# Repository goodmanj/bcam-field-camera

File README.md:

# BCam - Magnetic Field Camera

## About
BCam lets you see see invisible magnetic fields!  It uses an array of magnetic field sensors to map out the strength and direction of magnetic fields passing through it, displaying the fields on an LCD screen in realtime.  It can sense strong permanent magnets and electromagnets, as well as the weak fields from single current-carrying wires, and the Earth's magnetic field.

BCam is based on the [RP2040 Raspberry Pi Pico](https://www.raspberrypi.com/documentation/microcontrollers/pico-series.html) microcontroller, the [TMAG5273](https://www.ti.com/product/TMAG5273) Hall-effect magnetic field sensor, and the [ILI9488](http://www.lcdwiki.com/3.5inch_SPI_Module_ILI9488_SKU:MSP3520) touch LCD screen.  

BCam was originally designed as a teaching tool for physics classrooms.  The [documentation](doc/) includes demos, lab handouts, and other teaching material.

## Build your own!

This repo contains everything you need to build a BCam:
* [2d/](2d/): 2-d design files (label graphics)
* [pcb/](pcb/): Printed circuit board files
* [src/](src/): Arduino source code
* [cad/](cad/): 3-d design files
* [doc/](doc/): Documentation
* [bom.md](bom.md): Bill of materials

BCam is designed to be built by hand.  All surface-mount parts are hand-solderable (some skill required).  The case is 3-d printed.  You can use a desktop CNC machine to mill your own printed circuit board, or have it made by an online board manufacturer such as [JLCPCB](https://jlcpcb.com/), [PCBWay](https://www.pcbway.com/), or [OSHPark](https://oshpark.com/).

BCam was originally developed as a project for [Fab Academy](https://fabacademy.org/), a hands-on global class in rapid prototyping and digital fabrication.  The original project documentation is [archived at Fab Academy's site](https://fabacademy.org/2023/labs/wheaton/students/jason-goodman/final-project/index.html), but is superseded by this repo.

## Copyright and License

Copyright (c) 2023-2025 Jason Goodman <jcgoodman@gmail.com>

This work is licensed under a
[Creative Commons Attribution-NonCommercial-ShareAlike 4.0 International License][cc-by-nc-sa].

[![CC BY-NC-SA 4.0][cc-by-nc-sa-image]][cc-by-nc-sa]

[cc-by-nc-sa]: http://creativecommons.org/licenses/by-nc-sa/4.0/
[cc-by-nc-sa-image]: https://licensebuttons.net/l/by-nc-sa/4.0/88x31.png

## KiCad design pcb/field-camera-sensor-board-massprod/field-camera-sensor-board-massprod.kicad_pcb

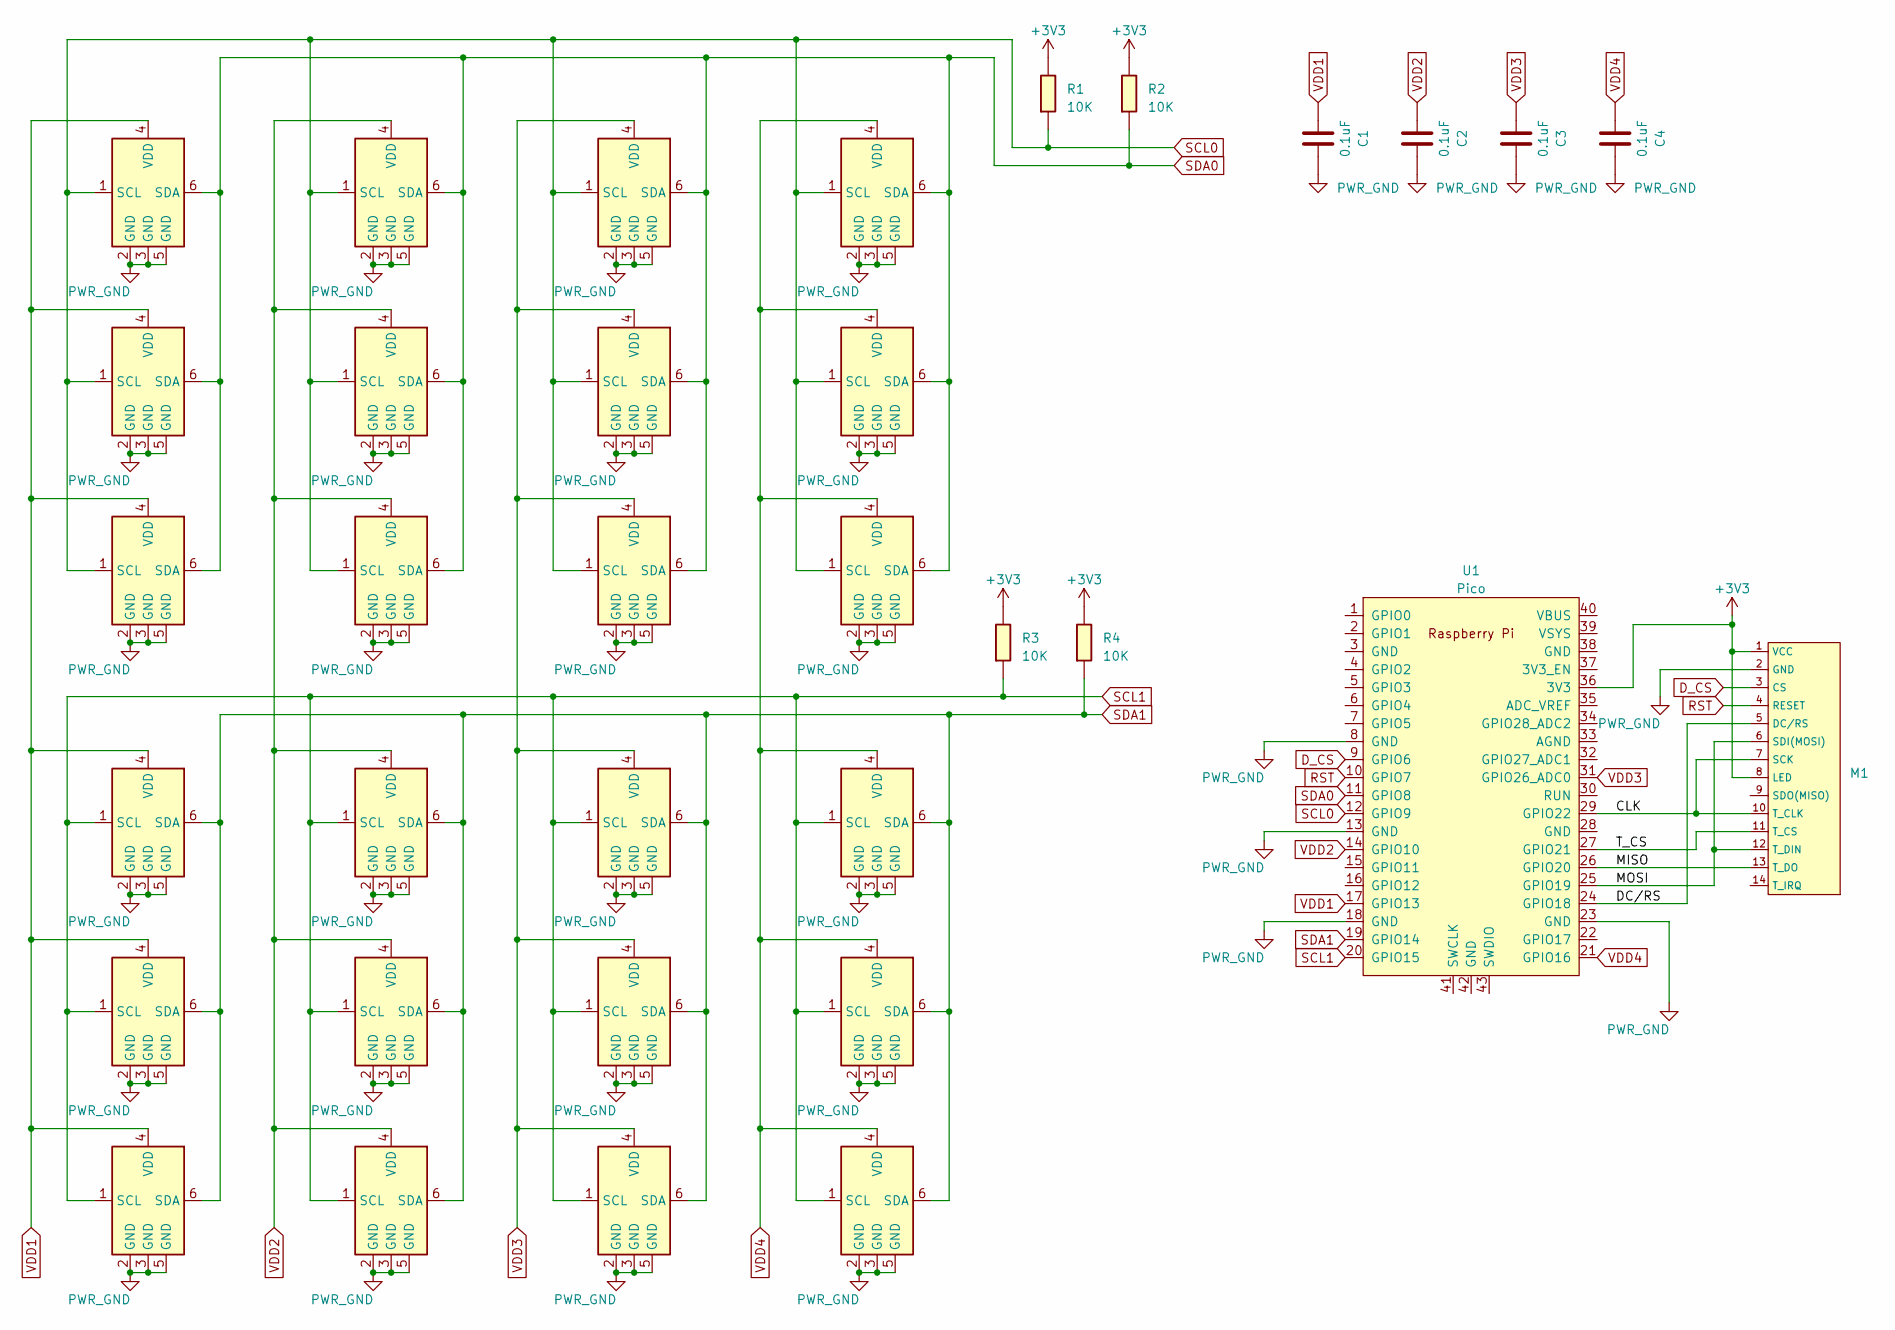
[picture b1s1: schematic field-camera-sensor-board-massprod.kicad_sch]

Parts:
C1, C2, C3, C4: 0.1uF; C_1206
M1: TFT-3.5-480x320-MSP3520-ILI9488
R1, R2, R3, R4: 10K; R_1206
U0A1, U0A2, U0A3, U0A4, U0B1, U0B2, U0B3, U0B4, U0C1, U0C2, U0C3, U0C4, U1A1, U1A2, U1A3, U1A4, U1B1, U1B2, U1B3, U1B4, U1C1, U1C2, U1C3, U1C4: Sensor_HallEffect_XYZ; TSOT-23-6
U1: Pico; RPi_Pico_SMD_TH

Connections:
+3V3: M1.1 (VCC), M1.8 (LED), R1.1, R2.1, R3.1, R4.1, U1.36 (3V3)
/CLK: M1.7 (SCK), M1.10 (T_CLK), U1.29 (GPIO22)
/DC/RS: M1.5 (DC/RS), U1.24 (GPIO18)
/MISO: M1.13 (T_DO), U1.26 (GPIO20)
/MOSI: M1.6 (SDI(MOSI)), M1.12 (T_DIN), U1.25 (GPIO19)
/T_CS: M1.11 (T_CS), U1.27 (GPIO21)
D_CS: M1.3 (CS), U1.9 (GPIO6)
PWR_GND: C1.2, C2.2, C3.2, C4.2, M1.2 (GND), U0A1.2 (GND), U0A1.3 (GND), U0A1.5 (GND), U0A2.2 (GND), U0A2.3 (GND), U0A2.5 (GND), U0A3.2 (GND), U0A3.3 (GND), U0A3.5 (GND), U0A4.2 (GND), U0A4.3 (GND), U0A4.5 (GND), U0B1.2 (GND), U0B1.3 (GND), U0B1.5 (GND), U0B2.2 (GND), U0B2.3 (GND), U0B2.5 (GND), U0B3.2 (GND), U0B3.3 (GND), U0B3.5 (GND), U0B4.2 (GND), U0B4.3 (GND), U0B4.5 (GND), U0C1.2 (GND), U0C1.3 (GND), U0C1.5 (GND), U0C2.2 (GND), U0C2.3 (GND), U0C2.5 (GND), U0C3.2 (GND), U0C3.3 (GND), U0C3.5 (GND), U0C4.2 (GND), U0C4.3 (GND), U0C4.5 (GND), U1.8 (GND), U1.13 (GND), U1.18 (GND), U1.23 (GND), U1A1.2 (GND), U1A1.3 (GND), U1A1.5 (GND), U1A2.2 (GND), U1A2.3 (GND), U1A2.5 (GND), U1A3.2 (GND), U1A3.3 (GND), U1A3.5 (GND), U1A4.2 (GND), U1A4.3 (GND), U1A4.5 (GND), U1B1.2 (GND), U1B1.3 (GND), U1B1.5 (GND), U1B2.2 (GND), U1B2.3 (GND), U1B2.5 (GND), U1B3.2 (GND), U1B3.3 (GND), U1B3.5 (GND), U1B4.2 (GND), U1B4.3 (GND), U1B4.5 (GND), U1C1.2 (GND), U1C1.3 (GND), U1C1.5 (GND), U1C2.2 (GND), U1C2.3 (GND), U1C2.5 (GND), U1C3.2 (GND), U1C3.3 (GND), U1C3.5 (GND), U1C4.2 (GND), U1C4.3 (GND), U1C4.5 (GND)
RST: M1.4 (RESET), U1.10 (GPIO7)
SCL0: R1.2, U0A1.1 (SCL), U0A2.1 (SCL), U0A3.1 (SCL), U0A4.1 (SCL), U0B1.1 (SCL), U0B2.1 (SCL), U0B3.1 (SCL), U0B4.1 (SCL), U0C1.1 (SCL), U0C2.1 (SCL), U0C3.1 (SCL), U0C4.1 (SCL), U1.12 (GPIO9)
SCL1: R3.2, U1.20 (GPIO15), U1A1.1 (SCL), U1A2.1 (SCL), U1A3.1 (SCL), U1A4.1 (SCL), U1B1.1 (SCL), U1B2.1 (SCL), U1B3.1 (SCL), U1B4.1 (SCL), U1C1.1 (SCL), U1C2.1 (SCL), U1C3.1 (SCL), U1C4.1 (SCL)
SDA0: R2.2, U0A1.6 (SDA), U0A2.6 (SDA), U0A3.6 (SDA), U0A4.6 (SDA), U0B1.6 (SDA), U0B2.6 (SDA), U0B3.6 (SDA), U0B4.6 (SDA), U0C1.6 (SDA), U0C2.6 (SDA), U0C3.6 (SDA), U0C4.6 (SDA), U1.11 (GPIO8)
SDA1: R4.2, U1.19 (GPIO14), U1A1.6 (SDA), U1A2.6 (SDA), U1A3.6 (SDA), U1A4.6 (SDA), U1B1.6 (SDA), U1B2.6 (SDA), U1B3.6 (SDA), U1B4.6 (SDA), U1C1.6 (SDA), U1C2.6 (SDA), U1C3.6 (SDA), U1C4.6 (SDA)
VDD1: C1.1, U0A1.4 (VDD), U0B1.4 (VDD), U0C1.4 (VDD), U1.17 (GPIO13), U1A1.4 (VDD), U1B1.4 (VDD), U1C1.4 (VDD)
VDD2: C2.1, U0A2.4 (VDD), U0B2.4 (VDD), U0C2.4 (VDD), U1.14 (GPIO10), U1A2.4 (VDD), U1B2.4 (VDD), U1C2.4 (VDD)
VDD3: C3.1, U0A3.4 (VDD), U0B3.4 (VDD), U0C3.4 (VDD), U1.31 (GPIO26_ADC0), U1A3.4 (VDD), U1B3.4 (VDD), U1C3.4 (VDD)
VDD4: C4.1, U0A4.4 (VDD), U0B4.4 (VDD), U0C4.4 (VDD), U1.21 (GPIO16), U1A4.4 (VDD), U1B4.4 (VDD), U1C4.4 (VDD)

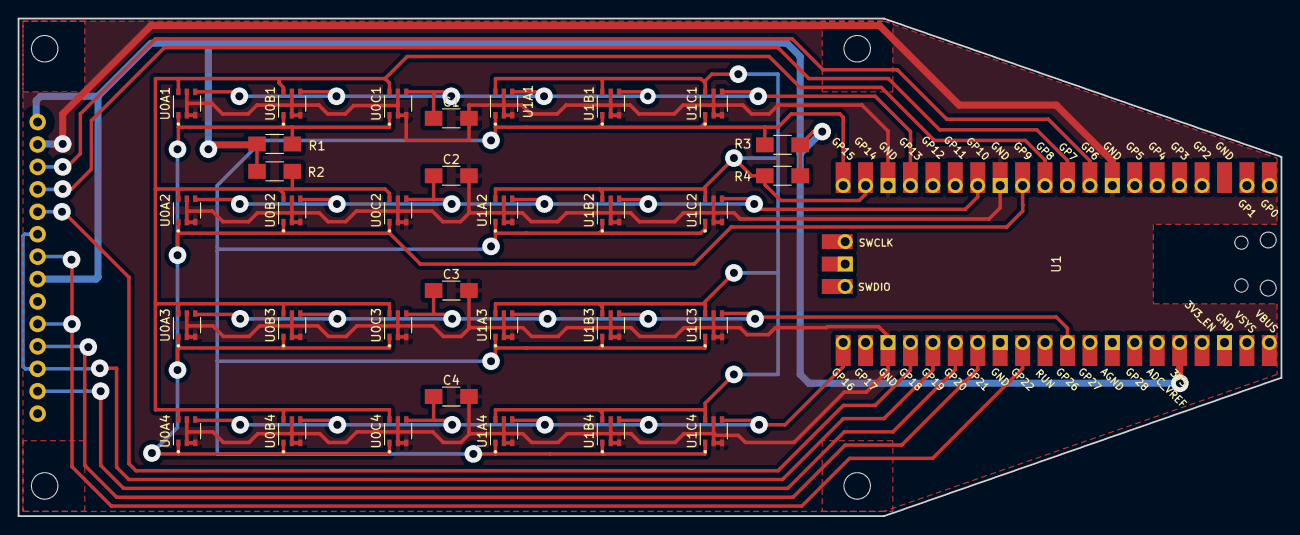
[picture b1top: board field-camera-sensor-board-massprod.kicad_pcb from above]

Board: 2 copper layers, 143.0 x 56.3 mm, 34 parts (0 on the bottom side), 17 nets.

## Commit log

2025-01-12 First copy from Fab Academy repo
2025-01-12 First README
2025-01-12 License twiddling
2025-01-12 Readme, bom
2025-01-13 Test for sensor availability
2025-01-13 availability bugfix
